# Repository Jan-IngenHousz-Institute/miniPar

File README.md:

# Mini PAR meter - minimum tool to get a good numerical sense of light intensity

# Commands

Commands are sent as plain text terminated with `\n`. JSON mode is also supported — send a valid JSON object and the device will respond in JSON.

* `hello`
    - Response: `MiniPAR,1.1` (plain) / `{"device":"MiniPAR","version":"1.1"}` (JSON)
* `reboot`
    - Restarts the device. Prints boot info ending with `Ready`.
* `delay_ms,<value>`
    - Example: `delay_ms,500`
    - Blocks for `<value>` milliseconds, then responds with the delay value: `500` (plain) / `{"delay_ms":500}` (JSON). Missing/negative value is treated as `0`.
* `battery`
    - Response: `NaN` (plain) / `{"battery":"NaN"}` (JSON)
    - Battery measurement not yet implemented.
* `i2c_scan`
    - Response: comma-separated list of I2C addresses that ACK (e.g. `0x39`)
* `spec[,<count>]`
    - Response: `{"spectrometer":{"model":"AS7341","channels":{"f1_415":1.2345,"f2_445":6.7890,...},"par":123.45}}` (JSON) / `model,ch0,ch1,...,par` (plain)
    - Returns **basic counts** per channel: `raw_reading / gain / integration_time_ms` (counts per millisecond per gain unit). Values are comparable across different gain and integration-time settings.
    - ⚠️ Firmware ≤ 1.05 divided by the integration time in **seconds**, so these values were 1000× larger. Check `hello`'s firmware version if you interpret them.
    - Also includes the calculated PAR value (same as the `par` command), computed from this same reading.
    - `<count>` repeats the measurement that many times (omit, or `1`, for a single reading); each reading is printed as soon as it's taken. With `<count> > 1`: JSON response becomes an array of the single-reading objects (`[{"spectrometer":{...}},{"spectrometer":{...}},...]`); plain response is the single-reading lines joined with `;` on one line.
* `spec_raw`
    - Response: same format as `spec` but raw unscaled integer counts (no normalization applied).
* `spec_flash,<mA>`
    - Example: `spec_flash,10`
    - Dark read → LED on → lit read. Response: `dark:<values>;lit:<values>;diff:<values>` (plain).
* `spec_set_atime,<0-255>`
    - Set spectrometer ATIME integration register. Response: the value set.
* `spec_set_astep,<0-65534>`
    - Set spectrometer ASTEP register. Response: the value set.
* `spec_set_gain,<0-10 (AS7341) | 0-12 (AS7343)>`
    - Set spectrometer gain index. Response: the value set.
* `spec_status` or `status`
    - Response: `model=<name>,available=<0|1>,atime=<val>,astep=<val>,gain=<val>` (plain)
* `set_led,<mA>`
    - Example: `set_led,20`
    - Response: `{"spectrometer":{"led_current_ma":20}}` (JSON) / actual mA set (plain)
    - LED current capped at 20 mA.
* `par[,<count>]`
    - Response: `123.45`
    - PAR value in µmol/m²/s, scaled by linear calibration: `y = a·par_raw + b`
    - `<count>` repeats the measurement that many times (omit, or `1`, for a single reading); each reading is printed as soon as it's taken. With `<count> > 1`: JSON response becomes an array (`[{"par":1.2},{"par":3.4},...]`); plain response is the values joined with `;` on one line.
* `par_raw`
    - Response: `1.23`
    - Weighted dot product of **basic counts** (raw / gain / integration_time_ms) and per-channel PAR coefficients. Independent of gain and integration-time settings.
* `cal_par_slope,<value>`
    - Example: `cal_par_slope,10.0`
    - Response: `{"calibration":{"slope":10.0}}`
    - Set the `a` coefficient for `y = ax + b` scaling. Persisted to NVS.
* `cal_par_intercept,<value>`
    - Example: `cal_par_intercept,2.3`
    - Response: `{"calibration":{"intercept":2.3}}`
    - Set the `b` coefficient for `y = ax + b` scaling. Persisted to NVS.
* `get_cal_par`
    - Response: `{"calibration":{"slope":10.0,"intercept":2.3}}` (JSON) / `slope=10.0,intercept=2.3` (plain)
    - Get the current `a` (slope) and `b` (intercept) coefficients for `y = ax + b` scaling.
* `set_spec_coeff,<channel>,<value>`
    - Example: `set_spec_coeff,0,0.614975`
    - Response: `{"spectrometer_coeff":{"channel":0,"value":0.614975}}`
    - Set per-channel PAR coefficient (channel 0–17). Coefficients are applied to **basic counts** (raw / gain / integration_time_ms), so they must account for the desired normalization. Persisted to NVS.
    - Default coefficients are pre-scaled for the default AS7341 settings (ATIME=100, ASTEP=999, GAIN=2×); re-derive from calibration if defaults are changed.
    - Since firmware 1.06 these are per-millisecond basic counts, matching `basic_counts()` in [new_calibration_miniPAR/as7341_calibrate.py](new_calibration_miniPAR/as7341_calibrate.py) — upload host-fitted coefficients directly, with no factor of 1000. Coefficients written by an earlier firmware are rescaled once on the first 1.06 boot.
* `get_spec_coeff`
    - Response: `{"spectrometer_coeffs":{"channels":{"0":0.614975,"1":0.053037,...}}}`
    - Get all 18 per-channel PAR coefficients.
* `get_spec_coeff,<channel>`
    - Example: `get_spec_coeff,0`
    - Response: `{"spectrometer_coeff":{"channel":0,"value":0.614975}}`
    - Get a specific per-channel PAR coefficient.
* `set_name,<string>`
    - Response: `{"device_name":"MyDevice"}`
    - Set custom device name. Persisted to NVS.
* `get_name`
    - Response: `{"device_name":"MyDevice"}`
    - Get current device name.

## BME280 (optional temperature/pressure/humidity sensor)

Detected automatically at boot (I2C address `0x76` or `0x77`); all commands below respond with `error:not_available` (plain) / `{"bme280":{"error":"not_available"}}` (JSON) if no BME280 is fitted. Temperature, pressure, and humidity are all enabled by default, at the highest oversampling (x16), IIR filter off, one-shot read mode.

* `bme_status`
    - Response (plain): `continuous=<0|1>,continuous_active=<0|1>,temp_comp=<value>,temp_en=<0|1>,temp_osrs=<0-5>,press_en=<0|1>,press_osrs=<0-5>,hum_en=<0|1>,hum_osrs=<0-5>,iir=<0-4>`
    - Response (JSON): `{"bme280_status":{"available":true,"continuous_mode":false,"continuous_active":false,"temperature_compensation_c":0.00,"temperature":{"enabled":true,"oversampling":5},"pressure":{"enabled":true,"oversampling":5},"humidity":{"enabled":true,"oversampling":5},"iir_filter":0}}`
* `bme_set_temp_enable,<0|1>`
    - Enable/disable temperature in `bme_get_tph` output. Temperature is still sampled internally regardless (pressure/humidity compensation depend on it) — this only affects reporting.
* `bme_set_press_enable,<0|1>`
    - Enable/disable pressure in `bme_get_tph` output.
* `bme_set_hum_enable,<0|1>`
    - Enable/disable humidity in `bme_get_tph` output.
* `bme_set_temp_oversample,<0-5>`
    - Oversampling: `0`=off (clamped to `1`, since temperature must always be sampled), `1`=x1, `2`=x2, `3`=x4, `4`=x8, `5`=x16 (default).
* `bme_set_press_oversample,<0-5>`
    - Same scale as above; `0`=channel skipped by the sensor.
* `bme_set_hum_oversample,<0-5>`
    - Same scale as above; `0`=channel skipped by the sensor.
* `bme_set_iir,<0-4>`
    - IIR filter coefficient: `0`=off (default), `1`=x2, `2`=x4, `3`=x8, `4`=x16.
* `bme_set_continuous,<0|1>`
    - `0` (default) = one-shot: every `bme_get_tph` call takes its own forced-mode measurement.
    - `1` = continuous: the chip free-runs in normal mode; `bme_get_tph` blocks only on the first call after enabling (waiting for that first conversion), then returns whatever the chip's background cycle last produced.
* `bme_set_temp_comp,<value>`
    - Set the temperature compensation offset in °C, added to every raw temperature reading (and folded into the pressure/humidity compensation math) to null out self-heating bias. Persisted to NVS.
* `bme_get_temp_comp`
    - Response: current temperature compensation offset in °C.
* `bme_get_tph[,<count>]` (alias: `tph[,<count>]`)
    - Response (plain): `<temperature_c>,<pressure_hpa>,<humidity_pct>` — positional CSV, blank field for a disabled channel.
    - Response (JSON): `{"bme280":{"temperature_c":23.45,"pressure_hpa":1013.25,"humidity_pct":45.20}}` — `null` for a disabled channel.
    - Behavior depends on `bme_set_continuous`: one-shot mode (default) takes a fresh forced-mode reading every call; continuous mode waits for the first conversion only on the first call after being enabled, then returns the most recent free-running reading on every call after that.
    - `<count>` repeats the measurement that many times (omit, or `1`, for a single reading); each reading is printed as soon as it's taken. With `<count> > 1`: JSON response becomes an array of the single-reading objects; plain response is the single-reading CSV rows joined with `;` on one line.

# Status LED (GPIO 10)

The LED on GPIO 10 provides a visual indication of spectrometer state:

| LED state | Meaning |
|-----------|---------|
| Off | No spectrometer detected at boot |
| Solid on | Spectrometer detected, all channels within range |
| Blinking 20 Hz | At least one spectrometer channel is saturated |

Saturation is checked automatically on every spectrometer read (`spec`, `spec_raw`, `par`, `par_raw`, etc.). The LED returns to solid-on as soon as the next read finds all channels within range. Reduce gain or integration time (`spec_set_gain`, `spec_set_atime`, `spec_set_astep`) to clear saturation.

# Protocol

* Command terminator: `\n` (`\r` is ignored)
* PAR units: µmol/m²/s
* **Basic counts**: `raw_reading / gain / integration_time_ms`, where `integration_time_ms = (ATIME+1) × (ASTEP+1) × 2.78e-3 ms`. Used by `spec`, `par`, and `par_raw` — values are gain/integration-time independent. This is the ams AN000633 §2.1 convention; firmware ≤ 1.05 used seconds instead, see [CALIBRATION.md](new_calibration_miniPAR/CALIBRATION.md#units-migration-firmware-105--106).
* **Default AS7341 settings**: ATIME=100, ASTEP=999, GAIN=2× (integration time ≈ 280.8 ms). Per-channel PAR coefficients stored in NVS are calibrated for basic counts at these defaults.

FW Design (L. Grabowski, L. Caracciolo),

HW Design (L. Grabowski)

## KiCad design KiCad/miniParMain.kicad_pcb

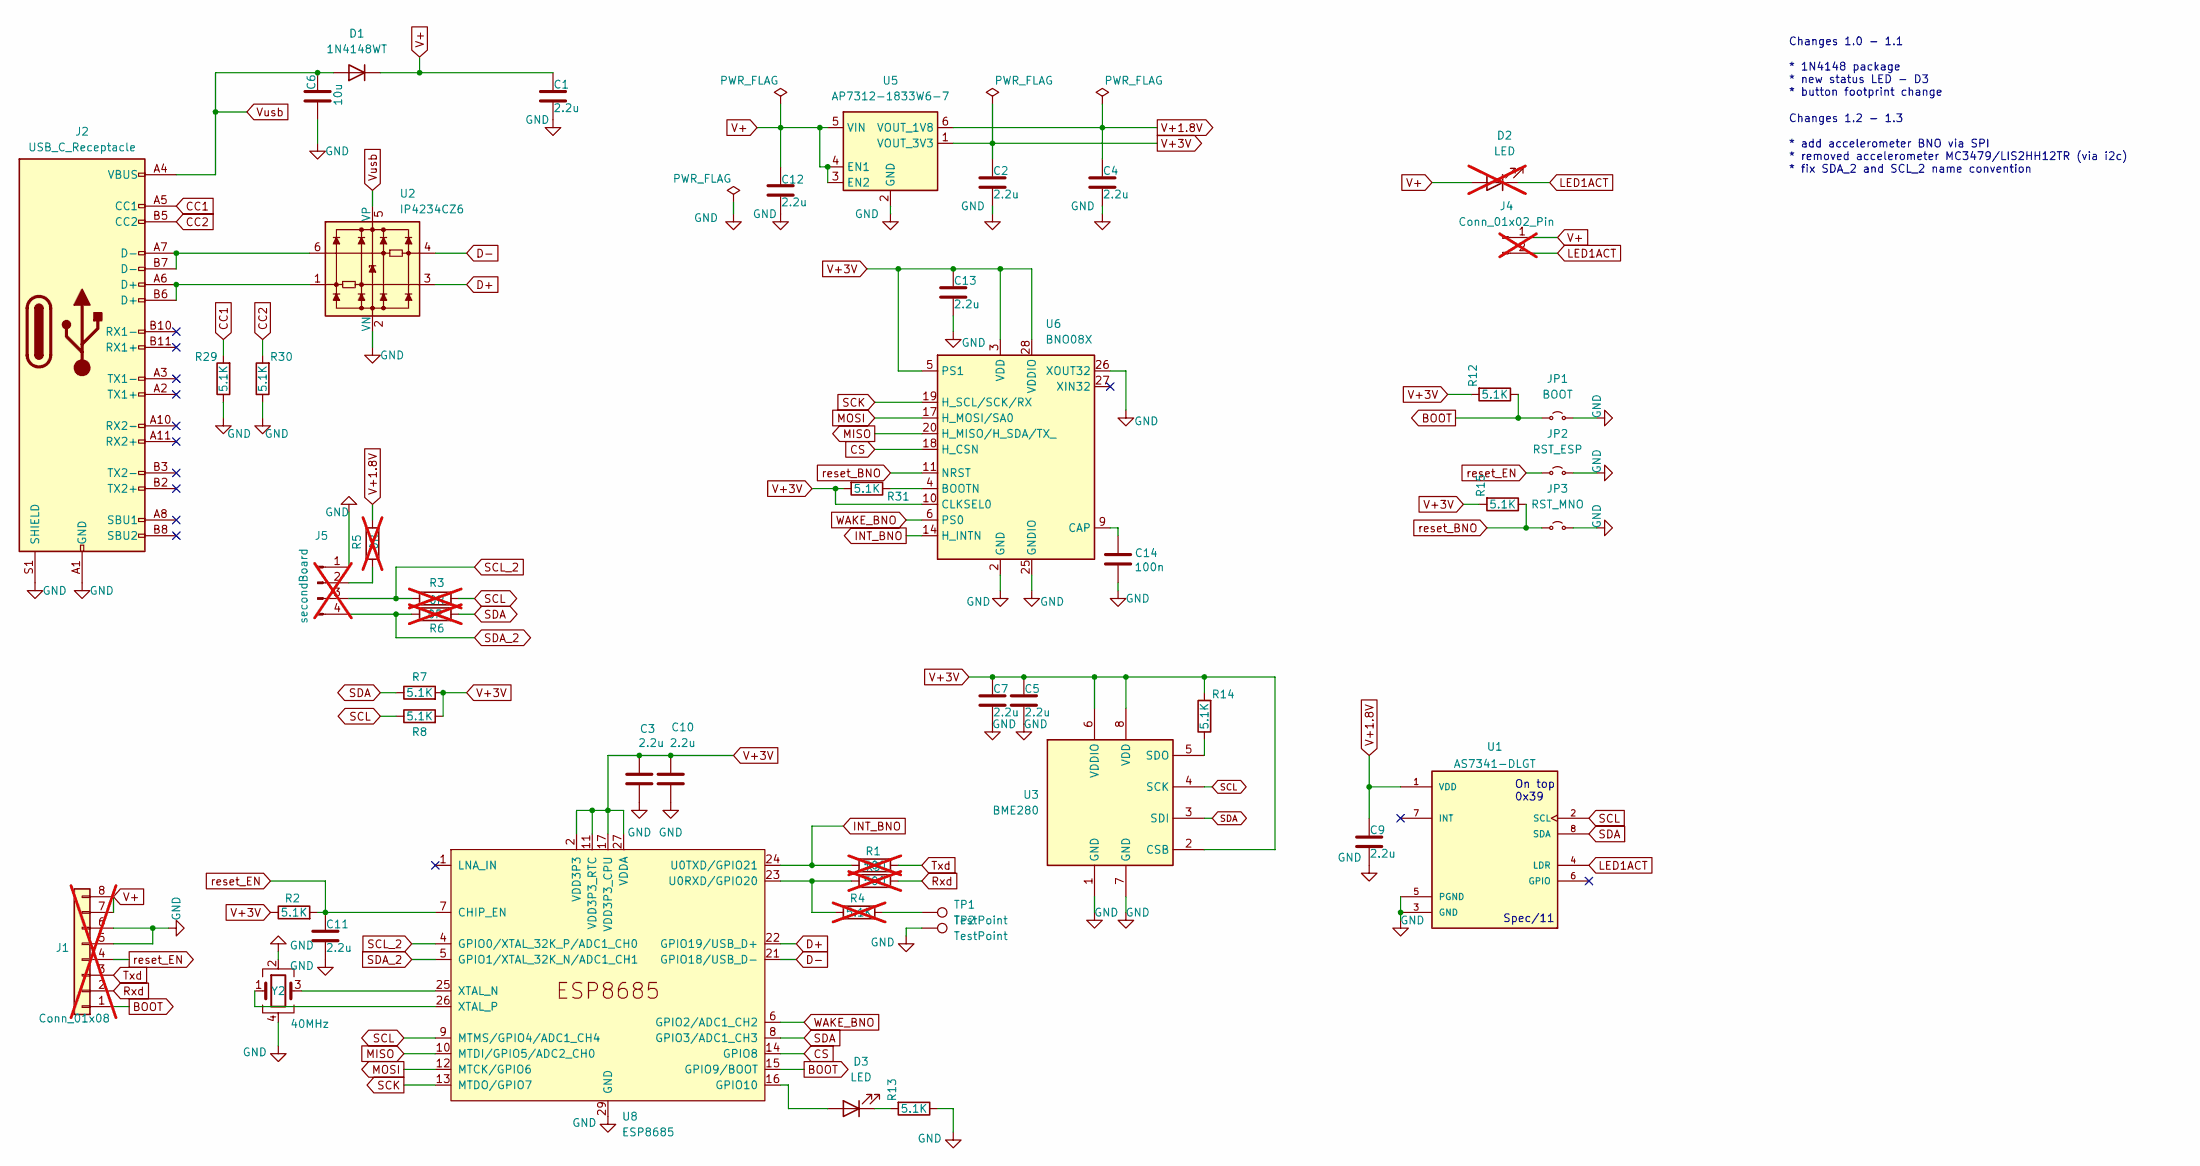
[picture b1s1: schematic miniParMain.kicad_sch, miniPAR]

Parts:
C1, C2, C3, C4, C5, C7, C9, C10, C11, C12, C13: 2.2u; C_0603_1608Metric_Pad1.08x0.95mm_HandSolder; Manufacturer_Part_Number GRT188R61H225KE13D
C6: 10u; C_0603_1608Metric; Manufacturer_Part_Number GRM188R61E106MA73J
C14: 100n; C_0603_1608Metric
D1: 1N4148WT; D_SOD-123; Manufacturer_Part_Number 1N4148W-TP
D2: LED; D_0805_2012Metric; not fitted
D3: LED; D_0805_2012Metric; Manufacturer_Part_Number LTST-C171KGKT
J1: Conn_01x08; Molex_5034800800_1x08-1MP_P0.50mm_Horizontal; not fitted
J2: USB_C_Receptacle; USB_C_Receptacle_HRO_TYPE-C-31-M-12; Manufacturer_Part_Number 12402012E212A
J4: Conn_01x02_Pin; PinHeader_1x02_P2.54mm_Vertical; not fitted
J5: secondBoard; PinSocket_1x04_P1.27mm_Vertical; not fitted
JP1: BOOT; SolderJumper-2_P1.3mm_Open_TrianglePad1.0x1.5mm
JP2: RST_ESP; SolderJumper-2_P1.3mm_Open_TrianglePad1.0x1.5mm
JP3: RST_MNO; SolderJumper-2_P1.3mm_Open_TrianglePad1.0x1.5mm
R1, R9: 500; R_0603_1608Metric_Pad0.98x0.95mm_HandSolder; not fitted
R2, R12, R13, R14, R15, R29, R30, R31: 5.1K; R_0603_1608Metric; Manufacturer_Part_Number 652-CR0603FX-5101ELF
R3, R5, R6: 0R; R_0603_1608Metric_Pad0.98x0.95mm_HandSolder; not fitted
R4: 5.1K; R_0603_1608Metric; Manufacturer_Part_Number 652-CR0603FX-5101ELF; not fitted
R7, R8: 5.1K; R_0603_1608Metric_Pad0.98x0.95mm_HandSolder
TP1, TP2: TestPoint; TestPoint_Pad_D1.0mm
U1: AS7341-DLGT; PSON80P310X200X110-8N; PARTREV V3
U2: IP4234CZ6; SC-74-6_1.55x2.9mm_P0.95mm; Manufacturer_Part_Number IP4234CZ6,115
U3: BME280; Bosch_LGA-8_2.5x2.5mm_P0.65mm_ClockwisePinNumbering
U5: AP7312-1833W6-7; TSOT-23-6; Manufacturer_Part_Number AP7312-1833W6-7
U6: BNO08X; LGA-28_5.2x3.8mm_P0.5mm
U8: ESP8685; QFN-28-1EP_4x4mm_P0.4mm_EP2.6x2.6mm; Manufacturer_Part_Number ESP8685H4
Y2: 40MHz; Crystal_SMD_2016-4Pin_2.0x1.6mm; Manufacturer_Part_Number ECS-400-8-47B2-CKM-TR

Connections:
BOOT: J1.1, JP1.1 (A), R12.1, U8.15 (GPIO9/BOOT)
CC1: J2.A5 (CC1_A5), R29.2
CC2: J2.B5 (CC2_B5), R30.2
CS: U6.18 (H_CSN), U8.14 (GPIO8)
D+: U2.3, U8.22 (GPIO19/USB_D+)
D-: U2.4, U8.21 (GPIO18/USB_D-)
GND: C1.2, C2.2, C3.2, C4.2, C5.2, C6.1, C7.2, C9.2, C10.2, C11.2, C12.2, C13.2, C14.1, J1.5, J1.6, J2.A1 (GND_A1), J2.A12 (GND_A12), J2.B1 (GND_B1), J2.B12 (GND_B12), J2.S1 (SHIELD), J2.SH (SHIELD_S1), J5.1, JP1.2 (B), JP2.2 (B), JP3.2 (B), R13.1, R29.1, R30.1, TP2.1 (1_1), U1.3 (GND), U1.5 (PGND), U2.2 (VN), U3.1 (GND), U3.7 (GND), U5.2 (GND), U6.2 (GND), U6.25 (GNDIO), U6.26 (XOUT32), U8.29 (GND), Y2.2, Y2.4
INT_BNO: R1.1, U6.14 (H_INTN), U8.24 (U0TXD/GPIO21)
LED1ACT: D2.1 (K), J4.2, U1.4 (LDR)
MISO: U6.20 (H_MISO/H_SDA/TX_), U8.10 (MTDI/GPIO5/ADC2_CH0)
MOSI: U6.17 (H_MOSI/SA0), U8.12 (MTCK/GPIO6)
unnamed: D3.2 (A), U8.16 (GPIO10)
unnamed: D3.1 (K), R13.2
unnamed: J1.2, R9.2
unnamed: J1.3, R1.2
unnamed: J2.A6 (D+_A6), J2.B6 (D+_B6), U2.1
unnamed: J2.A7 (D-_A7), J2.B7 (D-_B7), U2.6
unnamed: J5.2, R5.1
unnamed: R4.2, TP1.1 (1_1)
unnamed: R14.1, U3.5 (SDO)
unnamed: R31.1, U6.4 (BOOTN)
unnamed: C14.2, U6.9 (CAP)
unnamed: R4.1, R9.1, U8.23 (U0RXD/GPIO20)
unnamed: U8.25 (XTAL_N), Y2.3
unnamed: U8.26 (XTAL_P), Y2.1
SCK: U6.19 (H_SCL/SCK/RX), U8.13 (MTDO/GPIO7)
SCL: R3.2, R8.1, U1.2 (SCL), U3.4 (SCK), U8.9 (MTMS/GPIO4/ADC1_CH4)
SCL_2: J5.3, R3.1, U8.4 (GPIO0/XTAL_32K_P/ADC1_CH0)
SDA: R6.2, R7.1, U1.8 (SDA), U3.3 (SDI), U8.8 (GPIO3/ADC1_CH3)
SDA_2: J5.4, R6.1, U8.5 (GPIO1/XTAL_32K_N/ADC1_CH1)
V+: C1.1, C12.1, D1.1 (K), D2.2 (A), J1.7, J1.8, J4.1, U5.3 (EN2), U5.4 (EN1), U5.5 (VIN)
V+1.8V: C4.1, C9.1, R5.2, U1.1 (VDD), U5.6 (VOUT_1V8)
V+3V: C2.1, C3.1, C5.1, C7.1, C10.1, C13.1, R2.1, R7.2, R8.2, R12.2, R14.2, R15.2, R31.2, U3.2 (CSB), U3.6 (VDDIO), U3.8 (VDD), U5.1 (VOUT_3V3), U6.3 (VDD), U6.5 (PS1), U6.10 (CLKSEL0), U6.28 (VDDIO), U8.2 (VDD3P3), U8.3 (VDD3P3), U8.11 (VDD3P3_RTC), U8.17 (VDD3P3_CPU), U8.27 (VDDA), U8.28 (VDDA)
Vusb: C6.2, D1.2 (A), J2.A4 (VBUS_A4), J2.A9 (VBUS_A9), J2.B4 (VBUS_B4), J2.B9 (VBUS_B9), U2.5 (VP)
WAKE_BNO: U6.6 (PS0), U8.6 (GPIO2/ADC1_CH2)
reset_BNO: JP3.1 (A), R15.1, U6.11 (NRST)
reset_EN: C11.1, J1.4, JP2.1 (A), R2.2, U8.7 (CHIP_EN)

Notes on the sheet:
Spec/11
Changes 1.0 - 1.1 * 1N4148 package * new status LED - D3 * button footprint change
On top 0x39
Changes 1.2 - 1.3 * add accelerometer BNO via SPI * removed accelerometer MC3479/LIS2HH12TR (via i2c) * fix SDA_2 and SCL_2 name convention

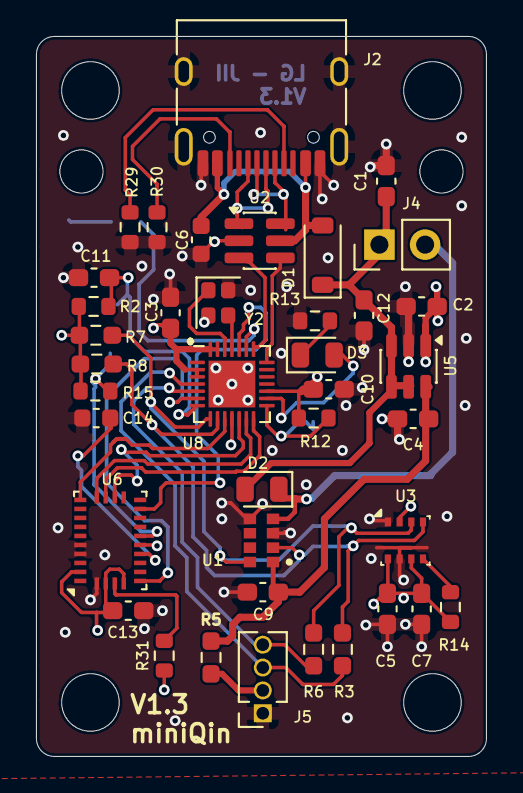
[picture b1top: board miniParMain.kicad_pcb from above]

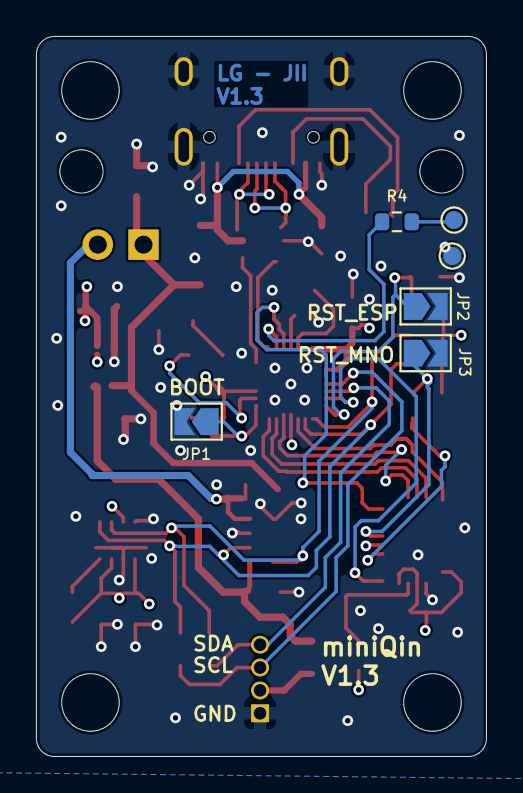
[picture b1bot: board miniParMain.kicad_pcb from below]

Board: 4 copper layers, 25.0 x 40.0 mm, 45 parts (6 on the bottom side), 35 nets.

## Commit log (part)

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2026-04-07 fix commit
2026-04-08 before merging with LG
2026-04-08 move FW files to subdirectory
2026-04-13 cover whole PCB
2026-04-13 add calibration fixture
2026-04-15 clean up of schematics - mpn + bom
2026-04-21 add device name to hanlde multiple devices
2026-04-21 cleaned calibration script, helpers moved to separate file
2026-04-21 modify script for 2 PAR sensors
2026-04-21 Add files via upload
    Corrected the old version - this one should fit better (keeps in mind some extra flex size when printing)
2026-04-21 Delete Case/Minipar_ambit_fixture.FCStd
    Removal of the old version
2026-05-03 working connection device to openJII by OTG usb-serial
2026-05-26 separate raw and json commend processing
2026-05-28 script and result for the angular callibration of the
2026-05-28 manual calibration
2026-05-28 reduce the gain by default
2026-05-28 clean manual calibration script
2026-05-28 adjusted the MiniParManualCalibration routine (measure at 3 different light intensity).
2026-06-01 first attempt with the halogen lamp
2026-06-01 MiniPAR + Licor Holder for cosine correction
2026-06-01 manual collection of channel reading for filtered light
2026-06-02 update of notebook for the multiple filter regression test
2026-06-03 spectral analysys clean param fitting and analysys
2026-06-03 add option to write and read the par spectral coefficients in the FW
2026-06-09 update of data collection script
2026-06-09 calibrate_spec stabilization
2026-06-17 cleanup and paramaeter update
2026-06-17 update compiled file
2026-06-29 par reading based on basic count, add LED power and saturation indicator
